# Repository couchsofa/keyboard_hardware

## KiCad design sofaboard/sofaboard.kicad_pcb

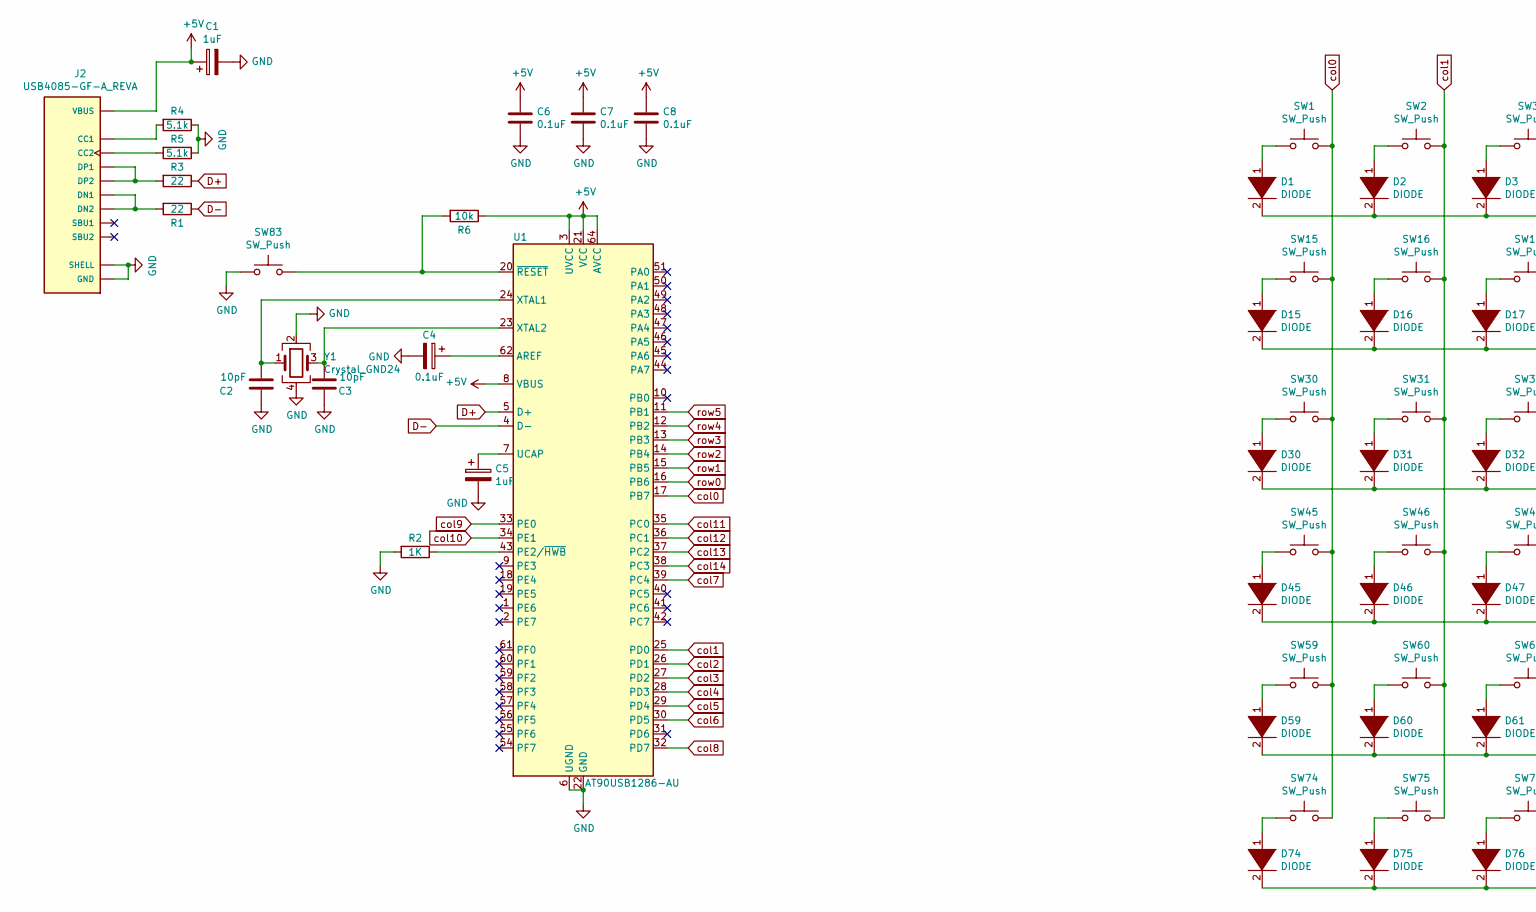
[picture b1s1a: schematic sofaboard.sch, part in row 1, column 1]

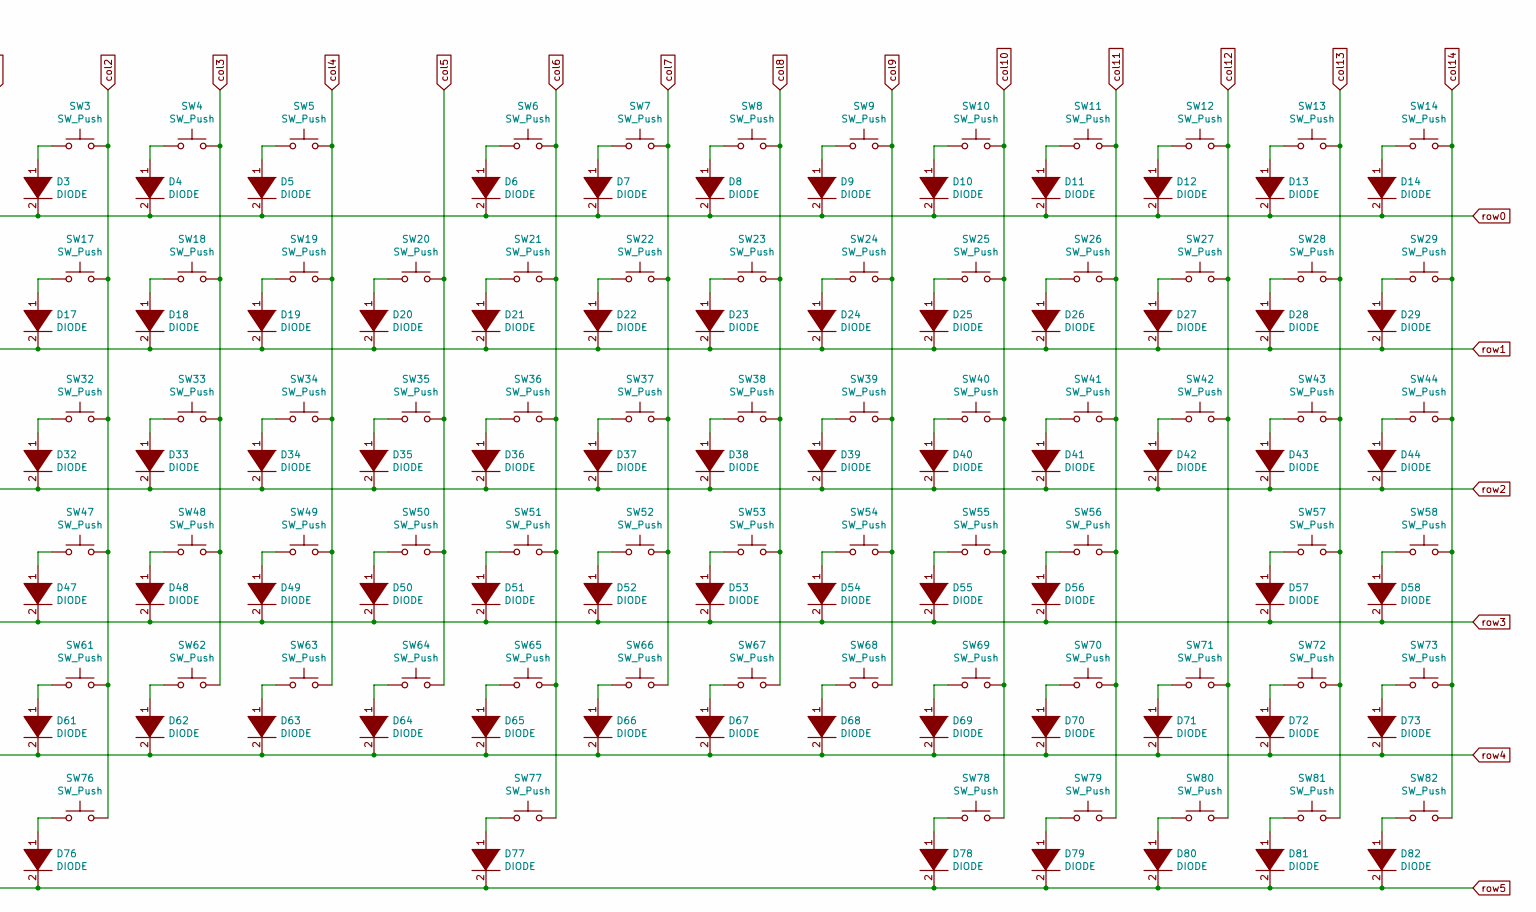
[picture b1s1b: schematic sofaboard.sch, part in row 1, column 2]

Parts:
C1, C5: 1uF; C_0805_2012Metric_Pad1.15x1.40mm_HandSolder
C2, C3: 10pF; C_0805_2012Metric_Pad1.15x1.40mm_HandSolder
C4, C6, C7, C8: 0.1uF; C_0805_2012Metric_Pad1.15x1.40mm_HandSolder
D1, D2, D3, D4, D5, D6, D7, D8, D9, D10, D11, D12, D13, D14, D15, D16, D17, D18, D19, D20, D21, D22, D23, D24, D25, D26, D27, D28, D29, D30, D31, D32, D33, D34, D35, D36, D37, D38, D39, D40, D41, D42, D43, D44, D45, D46, D47, D48, D49, D50, D51, D52, D53, D54, D55, D56, D57, D58, D59, D60, D61, D62, D63, D64, D65, D66, D67, D68, D69, D70, D71, D72, D73, D74, D75, D76, D77, D78, D79, D80, D81, D82: DIODE; D_SOT-23_ANK
J2: USB4085-GF-A_REVA; GCT_USB4085-GF-A_REVA; PARTREV A2
R1, R3: 22; R_0805_2012Metric
R2: 1K; R_0805_2012Metric_Pad1.15x1.40mm_HandSolder
R4, R5: 5.1k; R_0805_2012Metric
R6: 10k; R_0805_2012Metric
SW1, SW2, SW3, SW4, SW5, SW6, SW7, SW8, SW9, SW10, SW11, SW12, SW13, SW14, SW15, SW16, SW17, SW18, SW19, SW20, SW21, SW22, SW23, SW24, SW25, SW26, SW27, SW28, SW29, SW30, SW31, SW32, SW33, SW34, SW35, SW36, SW37, SW38, SW39, SW40, SW41, SW42, SW43, SW44, SW45, SW46, SW47, SW48, SW49, SW50, SW51, SW52, SW53, SW54, SW55, SW56, SW57, SW58, SW59, SW60, SW61, SW62, SW63, SW64, SW65, SW66, SW67, SW68, SW69, SW70, SW71, SW72, SW73, SW74, SW75, SW76, SW77, SW78, SW79, SW80, SW81, SW82: SW_Push; SW_Cherry_MX1A_1.00u_Plate_clean
SW83: SW_Push; SW_PUSH_6mm_H5mm
U1: AT90USB1286-AU; TQFP-64_14x14mm_P0.8mm
Y1: Crystal_GND24; 16MHz Crystal

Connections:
+5V: C1.1, C6.1, C7.1, C8.1, J2.A4 (VBUS), J2.A9 (VBUS), J2.B4 (VBUS), J2.B9 (VBUS), R6.1, U1.3 (UVCC), U1.8 (VBUS), U1.21 (VCC), U1.52 (VCC), U1.64 (AVCC)
D+: R3.1, U1.5 (D+)
D-: R1.1, U1.4 (D-)
GND: C1.2, C2.1, C3.1, C4.2, C5.2, C6.2, C7.2, C8.2, J2.A1 (GND), J2.A12 (GND), J2.B1 (GND), J2.B12 (GND), J2.P1 (SHELL), J2.P2 (SHELL), J2.P3 (SHELL), J2.P4 (SHELL), R2.2, R4.1, R5.1, SW83.1, U1.6 (UGND), U1.22 (GND), U1.53 (GND), U1.63 (GND), Y1.2, Y1.4
unnamed: C2.2, U1.24 (XTAL1), Y1.1
unnamed: C3.2, U1.23 (XTAL2), Y1.3
unnamed: C4.1, U1.62 (AREF)
unnamed: C5.1, U1.7 (UCAP)
unnamed: D1.1 (K), SW1.1
unnamed: D2.1 (K), SW2.1
unnamed: D3.1 (K), SW3.1
unnamed: D4.1 (K), SW4.1
unnamed: D5.1 (K), SW5.1
unnamed: D6.1 (K), SW6.1
unnamed: D7.1 (K), SW7.1
unnamed: D8.1 (K), SW8.1
unnamed: D9.1 (K), SW9.1
unnamed: D10.1 (K), SW10.1
unnamed: D11.1 (K), SW11.1
unnamed: D12.1 (K), SW12.1
unnamed: D13.1 (K), SW13.1
unnamed: D14.1 (K), SW14.1
unnamed: D15.1 (K), SW15.1
unnamed: D16.1 (K), SW16.1
unnamed: D17.1 (K), SW17.1
unnamed: D18.1 (K), SW18.1
unnamed: D19.1 (K), SW19.1
unnamed: D20.1 (K), SW20.1
unnamed: D21.1 (K), SW21.1
unnamed: D22.1 (K), SW22.1
unnamed: D23.1 (K), SW23.1
unnamed: D24.1 (K), SW24.1
unnamed: D25.1 (K), SW25.1
unnamed: D26.1 (K), SW26.1
unnamed: D27.1 (K), SW27.1
unnamed: D28.1 (K), SW28.1
unnamed: D29.1 (K), SW29.1
unnamed: D30.1 (K), SW30.1
unnamed: D31.1 (K), SW31.1
unnamed: D32.1 (K), SW32.1
unnamed: D33.1 (K), SW33.1
unnamed: D34.1 (K), SW34.1
unnamed: D35.1 (K), SW35.1
unnamed: D36.1 (K), SW36.1
unnamed: D37.1 (K), SW37.1
unnamed: D38.1 (K), SW38.1
unnamed: D39.1 (K), SW39.1
unnamed: D40.1 (K), SW40.1
unnamed: D41.1 (K), SW41.1
unnamed: D42.1 (K), SW42.1
unnamed: D43.1 (K), SW43.1
unnamed: D44.1 (K), SW44.1
unnamed: D45.1 (K), SW45.1
unnamed: D46.1 (K), SW46.1
unnamed: D47.1 (K), SW47.1
unnamed: D48.1 (K), SW48.1
unnamed: D49.1 (K), SW49.1
unnamed: D50.1 (K), SW50.1
unnamed: D51.1 (K), SW51.1
unnamed: D52.1 (K), SW52.1
unnamed: D53.1 (K), SW53.1
unnamed: D54.1 (K), SW54.1
unnamed: D55.1 (K), SW55.1
unnamed: D56.1 (K), SW56.1
unnamed: D57.1 (K), SW57.1
unnamed: D58.1 (K), SW58.1
unnamed: D59.1 (K), SW59.1
unnamed: D60.1 (K), SW60.1
unnamed: D61.1 (K), SW61.1
unnamed: D62.1 (K), SW62.1
unnamed: D63.1 (K), SW63.1
unnamed: D64.1 (K), SW64.1
unnamed: D65.1 (K), SW65.1
unnamed: D66.1 (K), SW66.1
unnamed: D67.1 (K), SW67.1
unnamed: D68.1 (K), SW68.1
unnamed: D69.1 (K), SW69.1
unnamed: D70.1 (K), SW70.1
unnamed: D71.1 (K), SW71.1
unnamed: D72.1 (K), SW72.1
unnamed: D73.1 (K), SW73.1
unnamed: D74.1 (K), SW74.1
unnamed: D75.1 (K), SW75.1
unnamed: D76.1 (K), SW76.1
unnamed: D77.1 (K), SW77.1
unnamed: D78.1 (K), SW78.1
unnamed: D79.1 (K), SW79.1
unnamed: D80.1 (K), SW80.1
unnamed: D81.1 (K), SW81.1
unnamed: D82.1 (K), SW82.1
unnamed: J2.A5 (CC1), R4.2
unnamed: J2.A6 (DP1), J2.B6 (DP2), R3.2
unnamed: J2.A7 (DN1), J2.B7 (DN2), R1.2
unnamed: J2.B5 (CC2), R5.2
unnamed: R2.1, U1.43 (PE2/~HWB)
unnamed: R6.2, SW83.2, U1.20 (~RESET)
col0: SW1.2, SW15.2, SW30.2, SW45.2, SW59.2, SW74.2, U1.17 (PB7)
col1: SW2.2, SW16.2, SW31.2, SW46.2, SW60.2, SW75.2, U1.25 (PD0)
col2: SW3.2, SW17.2, SW32.2, SW47.2, SW61.2, SW76.2, U1.26 (PD1)
col3: SW4.2, SW18.2, SW33.2, SW48.2, SW62.2, U1.27 (PD2)
col4: SW5.2, SW19.2, SW34.2, SW49.2, SW63.2, U1.28 (PD3)
col5: SW20.2, SW35.2, SW50.2, SW64.2, U1.29 (PD4)
col6: SW6.2, SW21.2, SW36.2, SW51.2, SW65.2, SW77.2, U1.30 (PD5)
col7: SW7.2, SW22.2, SW37.2, SW52.2, SW66.2, U1.39 (PC4)
col8: SW8.2, SW23.2, SW38.2, SW53.2, SW67.2, U1.32 (PD7)
col9: SW9.2, SW24.2, SW39.2, SW54.2, SW68.2, U1.33 (PE0)
col10: SW10.2, SW25.2, SW40.2, SW55.2, SW69.2, SW78.2, U1.34 (PE1)
col11: SW11.2, SW26.2, SW41.2, SW56.2, SW70.2, SW79.2, U1.35 (PC0)
col12: SW12.2, SW27.2, SW42.2, SW71.2, SW80.2, U1.36 (PC1)
col13: SW13.2, SW28.2, SW43.2, SW57.2, SW72.2, SW81.2, U1.37 (PC2)
col14: SW14.2, SW29.2, SW44.2, SW58.2, SW73.2, SW82.2, U1.38 (PC3)
row0: D1.2 (A), D2.2 (A), D3.2 (A), D4.2 (A), D5.2 (A), D6.2 (A), D7.2 (A), D8.2 (A), D9.2 (A), D10.2 (A), D11.2 (A), D12.2 (A), D13.2 (A), D14.2 (A), U1.16 (PB6)
row1: D15.2 (A), D16.2 (A), D17.2 (A), D18.2 (A), D19.2 (A), D20.2 (A), D21.2 (A), D22.2 (A), D23.2 (A), D24.2 (A), D25.2 (A), D26.2 (A), D27.2 (A), D28.2 (A), D29.2 (A), U1.15 (PB5)
row2: D30.2 (A), D31.2 (A), D32.2 (A), D33.2 (A), D34.2 (A), D35.2 (A), D36.2 (A), D37.2 (A), D38.2 (A), D39.2 (A), D40.2 (A), D41.2 (A), D42.2 (A), D43.2 (A), D44.2 (A), U1.14 (PB4)
row3: D45.2 (A), D46.2 (A), D47.2 (A), D48.2 (A), D49.2 (A), D50.2 (A), D51.2 (A), D52.2 (A), D53.2 (A), D54.2 (A), D55.2 (A), D56.2 (A), D57.2 (A), D58.2 (A), U1.13 (PB3)
row4: D59.2 (A), D60.2 (A), D61.2 (A), D62.2 (A), D63.2 (A), D64.2 (A), D65.2 (A), D66.2 (A), D67.2 (A), D68.2 (A), D69.2 (A), D70.2 (A), D71.2 (A), D72.2 (A), D73.2 (A), U1.12 (PB2)
row5: D74.2 (A), D75.2 (A), D76.2 (A), D77.2 (A), D78.2 (A), D79.2 (A), D80.2 (A), D81.2 (A), D82.2 (A), U1.11 (PB1)

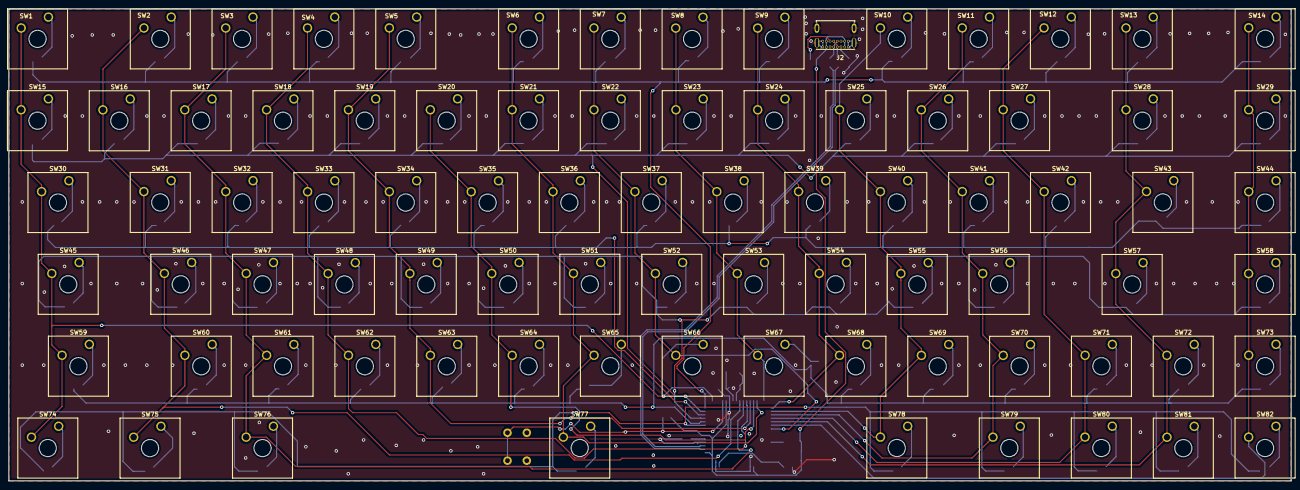
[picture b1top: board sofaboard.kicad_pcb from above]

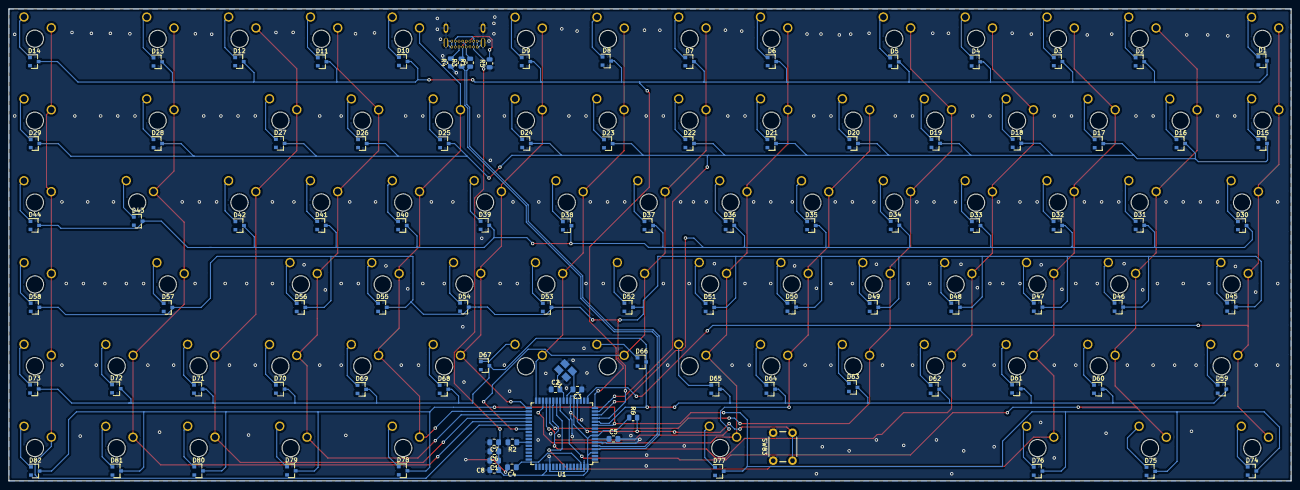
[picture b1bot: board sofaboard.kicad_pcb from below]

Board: 2 copper layers, 298.4 x 109.9 mm, 182 parts (99 on the bottom side), 117 nets.

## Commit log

2019-02-18 Update gitignore with kicad default
2019-02-18 Adds matrix schematic
2019-02-18 Adds microcontroller
2019-02-18 Fixes schematic layout
2019-02-18 Fixes annotations and no connection labels
2019-02-22 Assigns footprints
2019-02-22 Switch Placement
2019-02-22 Comonent Placement
2019-03-17 Started layouting
2019-03-17 Optimised routing
2019-03-17 Added GND planes
2019-03-23 Progress
2019-03-29 Change crystal footprint
2019-04-01 Changed crytal fp and added vias
2019-04-09 Made ready for ordering
2019-11-11 Improve routing and board dimensions
2021-04-10 Updated footprints
2021-10-28 reconnect diodes
2022-05-27 refit for order w/einball
2022-05-27 did more things for final order
